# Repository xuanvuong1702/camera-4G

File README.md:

# Camera 4G chạy pin — CAM4G

Camera ngoài trời, pin LFP 10 Ah, 4G, hồng ngoại, phát hiện chuyển động, ngủ sâu và đánh thức từ xa.

> **Bắt đầu đọc từ [`HANDOVER.md`](HANDOVER.md)** — tổng hợp trạng thái, đã/chưa kiểm chứng và việc còn lại.

## Trạng thái

| Hạng mục | Trạng thái |
|---|---|
| Yêu cầu & kiến trúc | Đã chốt |
| Schematic | **ERC 0 lỗi, 0 cảnh báo** |
| PCB | 100×70 mm, 4 lớp, 3 plane (GND/VBAT/+5V), **DRC 0 unconnected / 0 short / 0 clearance** — chỉ còn silk |
| Gerber + drill | Đã xuất, đóng gói `gerber/CAM4G-fab.zip` |
| BOM | 81 dòng, value đúng; kèm BOM mua hàng có MPN |
| CPL | 79 dòng (TP1/TP2 không paste — đúng) |
| Firmware Linux | **17/17 test pass** (mô phỏng) |
| Firmware MCU | **6/6 test host**, build ARM 1720 B |
| Cloud/app | Chưa bắt đầu |

## Quyết định quan trọng

- **720p**, IR ≤ 3 m, ghi local 7 h, không khí 40–45 °C.
- **Core1106G3 N256** (module 30×30, 112 pad) — không dùng dev board Pico Max.
- **Pin LFP 10 Ah** + BMS ngay từ đầu.
- **Vỏ nhôm đúc** — bắt buộc, Core1106 chỉ rated −20…+60 °C.
- **Modem Quectel EC200U-EU** qua UART, breakout cắm header J11; R32/R33 DNP.
- **Hai chế độ ngủ**: "canh gác nhanh" (~40–75 ngày, nhận lệnh 5–15 s) và "tiết kiệm tối đa" (nhiều tháng, chỉ PIR/lịch).
- Sạc bị cấm khi nhiệt độ pin > 40 °C.
- Board **100×70 mm** (80×55 không đủ chỗ cho 81 linh kiện).
- **v5**: sửa U3 sang SON DLC, shunt 0,01 Ω, J2 JST VH 10 A, Q3 AO3400A, VBUS_DET đúng, Q1–Q3 đã nối.

## Cấu trúc

```
4g-camera/
├── HANDOVER.md                   # tổng hợp trạng thái + việc còn lại
├── README.md
├── docs/
│   ├── 00–04                     # phân tích lịch sử (đã lưu)
│   ├── 05-simplification.md      # phương án giảm linh kiện
│   ├── 06-manufacturing.md       # hồ sơ gửi xưởng
│   ├── 07-test-plan.md           # kế hoạch kiểm tra 8 giai đoạn
│   ├── 08-bringup.md             # hướng dẫn cấp nguồn lần đầu
│   ├── 09-modem-ec200u.md        # chọn & đấu modem
│   ├── 10-readiness-audit.md     # rà soát sẵn sàng sản xuất
│   └── 11-cost-estimate.md       # dự tính chi phí lô 5 bộ
├── hardware/
│   ├── POWER.md                  # thiết kế khối nguồn
│   ├── wiring-v2-ipc.md          # kiến trúc & đấu dây
│   ├── bom-prototype-v3.csv      # BOM hệ thống
│   ├── datasheets/               # datasheet gốc
│   └── kicad/CAM4G/              # project, gerber, BOM, CPL, libs, tools
└── firmware/
    ├── linux/                    # app Python + 17 test
    └── mcu/                      # C + host test + target build (CMSIS)
```

## Hồ sơ gửi xưởng

| File | Vị trí |
|---|---|
| Gerber + drill | `hardware/kicad/CAM4G/gerber/CAM4G-fab.zip` |
| BOM | `hardware/kicad/CAM4G/CAM4G-bom.csv` |
| BOM mua hàng (MPN) | `hardware/kicad/CAM4G/CAM4G-bom-procurement.csv` |
| CPL | `hardware/kicad/CAM4G/CAM4G-cpl.csv` |
| Thông số & lắp ráp | `docs/06-manufacturing.md` |

## Nguyên tắc làm việc

- Mọi con số công suất/nhiệt là **ước tính** cho đến khi đo trên board thật.
- Không đoán số chân IC — sai một chân là hỏng board và mất 3 tuần.
- Không tuyên bố "chạy được" khi chưa có phép đo.

## Đã kiểm chứng / chưa

**Đã:** ERC, DRC, BOM↔board, Gerber, firmware test trên host, build ARM.

**Chưa:** chạy trên board thật, I2C slave, dòng ngủ, 7 h ghi ở 60 °C, 4G trên 3 nhà mạng, sạc LFP.

## Việc tiếp theo

1. Chọn mã LCSC cho thụ động (hoặc để JLCPCB map theo value + footprint).
2. Chốt breakout EC200U, camera 20-pin, pin 10 Ah, vỏ.
3. Đặt 5 bộ → làm theo `docs/08-bringup.md`.

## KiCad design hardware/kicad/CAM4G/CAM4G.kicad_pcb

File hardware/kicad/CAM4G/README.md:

# CAM4G — KiCad project (v4 final)

Carrier board cho Core1106 + modem EC200U-EU. **Thiết kế đã route xong và DRC sạch.**

## Trạng thái

| Hạng mục | Kết quả |
|---|---|
| Schematic | Hoàn chỉnh — U1 + nguồn + connector + MCU |
| ERC | **0 lỗi, 0 cảnh báo** |
| PCB | 100 × 70 mm, 4 lớp, **81 footprint** |
| Route | 1278 track + 183 via + plane In1 GND / In2 VBAT / B.Cu +5V |
| DRC | **0 unconnected, 0 short, 0 clearance, 0 track width, 0 copper edge** |
| Lỗi còn lại | 4 silk_edge_clearance + 2 silk_over_copper (chỉ in lụa) |
| Gerber | 28 file + drill, đóng gói `gerber/CAM4G-fab.zip` |
| BOM | 81 dòng, value đúng (lấy từ netlist) |
| CPL | 79 dòng (TP1/TP2 không paste — đúng) |

## File chính

| File | Nội dung |
|---|---|
| `CAM4G.kicad_pro` | Project KiCad 10 |
| `CAM4G.kicad_sch` | Schematic đầy đủ (khổ User 1400×1150) |
| `CAM4G.kicad_pcb` | PCB 100×70, 4 lớp, đã route |
| `CAM4G.kicad_dru` | Rule tuỳ chỉnh |
| `CAM4G.net` | Netlist (85 net chức năng) |
| `CAM4G-bom.csv` | BOM 81 dòng |
| `CAM4G-bom-procurement.csv` | BOM mua hàng, có MPN gợi ý |
| `CAM4G-cpl.csv` | Toạ độ dán |
| `gerber/` | Gerber + drill + `CAM4G-fab.zip` |
| `CAM4G-schematic-preview.pdf` | Xem trước schematic |
| `CAM4G-pcb-preview.pdf` | Xem trước PCB |
| `erc-final.rpt` / `drc-final.rpt` | Báo cáo cuối |
| `libs/` | Symbol Core1106, symbol nguồn, footprint, 3D |
| `tools/` | Script dựng board và nhập route |
| `NETLIST.md` | Bảng kết nối, pinout camera 20P |

## Thông số board

| Thông số | Giá trị |
|---|---|
| Kích thước | 100 × 70 mm |
| Số lớp | 4 |
| Độ dày | 1,6 mm |
| Đồng | 1 oz |
| Bề mặt | ENIG |
| Min trace | 0,15 mm (stub 0,1 mm) |
| Min clearance | 0,14 mm |
| Via | 0,45 mm / khoan 0,3 mm |
| Lỗ khoan | (3,5; 23,2), (95,5), (5,65), (95,65) |

## Các sửa đổi quan trọng

1. **Zone VBAT F.Cu toàn board bị export thành "plane"** → Freerouting bỏ qua net COMP_BOOST.
   Đã bỏ zone trước khi route, route lại, thêm zone B.Cu sau. **Đây là nguyên nhân 2 điểm COMP
   chưa nối tồn tại qua nhiều vòng.**
2. Footprint TPS61088 sửa theo land pattern TI RHL0020A: pad 0,24×0,6 tại ±1,525, EP 2,05.
3. Pad góc U2 giảm 0,24 → 0,23 mm để đủ clearance 0,15 mm (lệch 0,01 mm so với TI).
4. Lỗ khoan dời khỏi L1 và R21.
5. Netclass clearance hạ 0,2 → 0,14 mm; min track 0,1 mm cho stub MIPI.
6. U3 chuyển sang SON DLC 1,5×2 (datasheet); J2 JST VH 10 A; R7 0,01 Ω 2512; Q3 AO3400A; Q1–Q3 nối đúng chân; R34 → VBUS_5V.

## Quy trình dựng lại

```powershell
$py = "C:\Users\vuong\AppData\Local\Programs\KiCad\10.0\bin\python.exe"
$dir = "...\hardware\kicad\CAM4G"
& $py "$dir\tools\build_pcb.py"          # dựng board chưa route
& $py -c "import pcbnew; b=pcbnew.LoadBoard(r'...\CAM4G.kicad_pcb'); pcbnew.ExportSpecctraDSN(b, r'...\CAM4G.dsn')"
# route bằng Freerouting (jar Java 25)
& $py "$dir\tools\ses_import.py"          # nhập .ses
& $py "$dir\tools\post_route_fix.py"      # via + zone VBAT B.Cu
kicad-cli pcb drc ...
```

## Ghi chú

- **MIPI chưa kiểm soát impedance 100 Ω** — rủi ro nếu ảnh lỗi.
- Pad U2 0,23 mm thay vì 0,24 mm — trong dung sai hàn.
- Không còn file backup; lịch sử nằm trong git (`dev`).

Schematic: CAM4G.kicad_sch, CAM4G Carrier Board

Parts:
BT1: CR1220; Battery_Panasonic_CR1220-VCN_Vertical_CircularHoles
C1, C11, C13, C14: 10uF; C_0603_1608Metric
C2, C6, C12, C15, C16, C17, C19: 100nF; C_0603_1608Metric
C3: 3.3uF; C_0603_1608Metric
C4: 47uF; C_0603_1608Metric
C5: 2.2nF; C_0603_1608Metric
C7: 47nF; C_0603_1608Metric
C8: DNP; C_0603_1608Metric; not fitted
C9, C18: 1uF; C_0603_1608Metric
C10: 4.7uF; C_0603_1608Metric
D1: RED; LED_0603_1608Metric
D2: GRN; LED_0603_1608Metric
D3: PWR; LED_0603_1608Metric
D5, D6: BAT54; D_SOD-323
J1: USB-C; USB_C_Receptacle_HRO_TYPE-C-31-M-12
J2: BAT; JST_VH_B2P-VH_1x02_P3.96mm_Vertical
J3: CAM 20P; Hirose_FH12-20S-0.5SH_1x20-1MP_P0.50mm_Horizontal
J4: microSD; microSD_HC_Hirose_DM3AT-SF-PEJM5
J6: PIR; JST_XH_B3B-XH-A_1x03_P2.50mm_Vertical
J7: IR LED; JST_XH_B2B-XH-A_1x02_P2.50mm_Vertical
J8: IR-CUT; JST_XH_B2B-XH-A_1x02_P2.50mm_Vertical
J9, J10: DS18B20; JST_XH_B3B-XH-A_1x03_P2.50mm_Vertical
J11: MODEM; PinHeader_2x06_P1.27mm_Vertical
J12: DEBUG UART; PinHeader_1x03_P2.54mm_Vertical
J13: SWD; PinHeader_1x04_P2.54mm_Vertical
L1: 1.2uH; L_Bourns-SRN8040_8x8.15mm
L2: 2.2uH; L_Bourns-SRN4018
NTC1: 10k B3950; R_0603_1608Metric
Q1: AO3401; SOT-23
Q2: 2N3904; SOT-23
Q3: AO3400A; SOT-23
R1: 178k; R_0603_1608Metric
R2: 56k; R_0603_1608Metric
R3, R6: 267k; R_0603_1608Metric
R4: 64.9k; R_0603_1608Metric
R5: 10.5k; R_0603_1608Metric
R7: 0.01R; R_2512_6332Metric
R8, R9: 4.7k; R_0603_1608Metric
R10: 2.4k; R_0603_1608Metric
R11, R12, R21: 1k; R_0603_1608Metric
R13: 7.15k; R_0603_1608Metric
R14, R15: 5.1k; R_0603_1608Metric
R16, R18, R20: 100k; R_0603_1608Metric
R17, R23, R25, R34, R35: 10k; R_0603_1608Metric
R19: 100R; R_0603_1608Metric
R24, R31, R32, R33: 0R; R_0603_1608Metric
SW1: RESET; SW_SPST_B3S-1000
TP1: TP_3V3; TestPoint_Pad_1.5x1.5mm
TP2: TP_1V8; TestPoint_Pad_1.5x1.5mm
U1: Core1106; Core1106-SMT
U2: TPS61088; VQFN20_3.5
U3: TPS62840; DLC0008B
U4: INA226; MSOP-10_3x3mm_P0.5mm
U5: CN3058E; SOIC-8-1EP_3.9x4.9mm_P1.27mm_EP2.41x3.3mm
U6: STM32L011F4; TSSOP-20_4.4x6.5mm_P0.65mm

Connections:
/+3V3: C11.1, C12.1, C17.1, C18.1, D5.2 (A), J3.19, J3.20, J4.4 (VDD), J6.1, J9.1, J10.1, J11.11, J13.1, L2.2, R8.2, R9.2, R21.1, R23.1, U3.8 (VOS), U4.6 (VS), U6.5 (VDDA), U6.16 (VDD)
/+3V3_RTC: C16.1, D5.1 (K), D6.1 (K), U1.76 (VCC3V3_RTC)
/+5V_MODEM: J11.1, Q1.3 (D)
/+5V_SYS: C4.1, C9.1, J7.1, Q1.2 (S), R1.1, R16.1, U1.79 (VCC5V0_SYS), U1.80 (VCC5V0_SYS), U1.81 (VCC5V0_SYS), U2.14 (VOUT), U2.15 (VOUT), U2.16 (VOUT)
/BOOST_EN: U2.2 (EN), U6.11 (PA5)
/BOOT_BOOST: C6.1, U2.8 (BOOT)
/BT1_P: BT1.1 (+), D6.2 (A)
/BUCK_EN: R31.1, U3.4 (EN)
/CAM_MCLK: J3.2, U1.19 (VI_CIF_CLKO_M0/MIPI_CLK0_OUT/GPIO3_C4_d)
/CAM_MIPI_CK_N: J3.8, U1.9 (VI_CIF_D8_M0/MIPI_CSI_RX_CK0N/LVDS_RX_C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)
/CAM_MIPI_CK_P: J3.7, U1.10 (VI_CIF_D9_M0/MIPI_CSI_RX_CK0P/LVDS_RX_C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)
/CAM_MIPI_D0_N: J3.5, U1.11 (VI_CIF_CLKI_M0/MIPI_CSI_RX_D0N/LVDS_RX_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)
/CAM_MIPI_D0_P: J3.4, U1.12 (VI_CIF_HREF_M0/MIPI_CSI_RX_D0P/LVDS_RX_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)
/CAM_MIPI_D1_N: J3.11, U1.7 (VI_CIF_D6_M0/MIPI_CSI_RX_D1N/LVDS_RX_D1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)
/CAM_MIPI_D1_P: J3.10, U1.8 (VI_CIF_D7_M0/MIPI_CSI_RX_D1P/LVDS_RX_D1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)
/CAM_RESET: J3.16, U1.16 (VI_CIF_D11/UART5_TX_M2/I2C4_SCL_M2/GPIO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)
/CAM_SCL: J3.13, U1.15 (VI_CIF_D13/UART5_RTS_M2/I2C3_SCL_M2/GPI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)
/CAM_SDA: J3.14, U1.14 (VI_CIF_D14/UART5_CTS_M2/I2C3_SDA_M2/GPI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)
/CHG_DONE: D2.1 (K), U5.6 (DONE)
/CHG_STAT: D1.1 (K), U5.7 (CHRG)
/COMP_BOOST: C8.1, R5.1, U2.18 (COMP)
/COMP_MID: C5.1, R5.2
/DBG_RX: J12.2, U1.59 (UART0_TX_M0/PWM2_M0/GPIO0_A1_d)
/DBG_TX: J12.1, U1.58 (UART0_RX_M0/CLK_32K/CLK_REFOUT/RTC_CLKO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)
/FB_BOOST: R1.2, R2.1, U2.17 (FB)
/FSW_BOOST: R3.1, U2.3 (FSW)
/GND: BT1.2 (-), C1.2, C2.2, C3.2, C4.2, C5.2, C7.2, C8.2, C9.2, C10.2, C11.2, C12.2, C13.2, C14.2, C15.2, C16.2, C17.2, C18.2, C19.2, D3.1 (K), J1.A1 (GND), J1.A12 (GND), J1.B1 (GND), J1.B12 (GND), J1.SH (SHIELD), J2.2, J3.1, J3.3, J3.6, J3.9, J3.12, J3.15, J3.17, J3.18, J4.6 (VSS), J4.SH (SHIELD), J6.3, J9.3, J10.3, J11.2, J11.8, J11.12, J12.3, J13.4, NTC1.2, Q2.2 (E), Q3.2 (S), R2.2, R4.2, R6.2, R10.2, R14.2, R15.2, R18.2, R20.2, R24.2, R25.2, R35.2, SW1.2, U1.21 (GND), U1.25 (GND), U1.28 (GND), U1.29 (GND), U1.36 (GND), U1.47 (GND), U1.55 (GND), U1.56 (GND), U1.57 (GND), U1.75 (GND), U1.82 (GND), U1.83 (GND), U1.84 (GND), U1.89 (GND), U1.112 (GND), U2.11 (NC), U2.12 (NC), U2.13 (MODE), U2.20 (AGND), U2.21 (PGND), U3.1 (GND), U3.3 (MODE), U3.6 (STOP), U4.1 (A1), U4.2 (A0), U4.7 (GND), U5.3 (GND), U5.9 (EP), U6.15 (VSS)
/I2C_SCL: R9.1, U1.63 (I2C1_SCL_M0/UART1_RTS_M0/PWM5_M0/GPIO0_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), U4.5 (SCL), U6.17 (PA9)
/I2C_SDA: R8.1, U1.64 (I2C1_SDA_M0/UART1_CTS_M0/PWM6_M0/GPIO0_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), U4.4 (SDA), U6.18 (PA10)
/ILIM_BOOST: R4.1, U2.19 (ILIM)
/INA_ALERT: U4.3 (ALERT), U6.13 (PA7)
/IRCUT_A: J8.1, U1.70 (UART4_RX_M0/PWM3_IR_M1/GPIO1_B0_d)
/IRCUT_B: J8.2, U1.71 (UART4_TX_M0/PWM7_IR_M1/SPI1_CS1_M0/VI_C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)
/IR_GATE: Q3.1 (G), R19.2, R20.1
/IR_LED_K: J7.2, Q3.3 (D)
/IR_PWM: R19.1, U1.60 (PWM3_IR_M0/GPIO0_A2_d)
/ISET: R10.1, U5.2 (ISET)
/LED_CHG_A: D1.2 (A), R11.2
/LED_DONE_A: D2.2 (A), R12.2
/LED_PWR_A: D3.2 (A), R21.2
/MCU_BOOT0: R25.1, U6.1 (PB9)
/MCU_NRST: C19.1, U6.4 (NRST)
/MODEM_B: Q2.1 (B), R17.2, R18.1
/MODEM_EN: R17.1, U6.10 (PA4)
/MODEM_GATE: Q1.1 (G), Q2.3 (C), R16.2
/MODEM_PWRKEY: J11.5, U6.8 (PA2)
/MODEM_RESET: J11.7, U6.2 (PC14)
/MODEM_STATUS: J11.6, U6.9 (PA3)
/MODEM_UART_RX: J11.10, U1.69 (UART1_RX_M0/I2C0_SDA_M0/GPIO1_A4_d)
/MODEM_UART_TX: J11.9, U1.68 (UART1_TX_M0/I2C0_SCL_M0/GPIO1_A3_d)
/ONEWIRE: J9.2, J10.2, U6.7 (PA1)
/PIR_OUT: J6.2, U6.6 (PA0)
/RESET_N: C15.1, R23.2, SW1.1, U1.74 (NPOR)
/SD_CD: R24.1, U1.48 (SDMMC_DET/GPIO3_A1_u)
/SD_CLK: J4.5 (CLK), U1.54 (SDMMC_CLK/UART5_RTS_M0/I2C0_SCL_M2/JTAG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)
/SD_CMD: J4.3 (CMD), U1.53 (SDMMC_CMD/UART5_CTS_M0/I2C0_SDA_M2/JTAG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)
/SD_D0: J4.7 (DAT0), U1.49 (SDMMC_D0/UART2_RX_M0/PWM8_M0/GPIO3_A3_u)
/SD_D1: J4.8 (DAT1), U1.50 (SDMMC_D1/UART2_TX_M0/PWM9_M0/GPIO3_A2_u)
/SD_D2: J4.1 (DAT2), U1.51 (SDMMC_D2/UART5_RX_M0/JTAG_CPU_TCK_M0/JT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)
/SD_D3: J4.2 (DAT3/CD), U1.52 (SDMMC_D3/UART5_TX_M0/JTAG_CPU_TMS_M0/JT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)
/SOC_READY: U1.67 (PWM0_M0/CPU_AVS/VI_CIF_D0_M1/GPIO1_A2_d), U6.12 (PA6)
/SS_BOOST: C7.1, U2.10 (SS)
/SWCLK: J13.3, U6.20 (PA14)
/SWDIO: J13.2, U6.19 (PA13)
/SW_BOOST: C6.2, L1.2, R3.2, U2.4 (SW), U2.5 (SW), U2.6 (SW), U2.7 (SW)
/SW_BUCK: L2.1, U3.7 (SW)
/TEMP_NTC: NTC1.1, R13.1, U5.1 (TEMP)
/TP_1V8: TP2.1, U1.77 (VCC_1V8)
/TP_3V3: TP1.1, U1.78 (VCC_3V3)
/USB_CC1: J1.A5 (CC1), R14.1
/USB_CC2: J1.B5 (CC2), R15.1
/USB_DBG_DM: J1.A7 (D-), J1.B7 (D-)
/USB_DBG_DP: J1.A6 (D+), J1.B6 (D+)
/USB_DM: R33.1, U1.22 (USB_N)
/USB_DP: R32.1, U1.23 (USB_P)
/USB_MODEM_DM: J11.4, R33.2
/USB_MODEM_DP: J11.3, R32.2
/VBAT: C1.1, C2.1, C10.1, C14.1, L1.1, R7.2, R31.2, U2.9 (VIN), U3.2 (VIN), U4.8 (VBUS), U4.9 (IN-), U5.5 (BAT), U5.8 (FB)
/VBAT_BMS: J2.1, R7.1, U4.10 (IN+)
/VBAT_SENSE: U1.26 (SARADC_IN0/GPIO4_C0_z), U6.14 (PB1)
/VBUS_5V: C13.1, J1.A4 (VBUS), J1.A9 (VBUS), J1.B4 (VBUS), J1.B9 (VBUS), R11.1, R12.1, R13.2, R34.1, U5.4 (VIN)
/VBUS_DET: R34.2, R35.1, U1.24 (USB_VBUSDET)
/VCC_BOOST: C3.1, U2.1 (VCC)
/VSET_BUCK: R6.1, U3.5 (VSET)

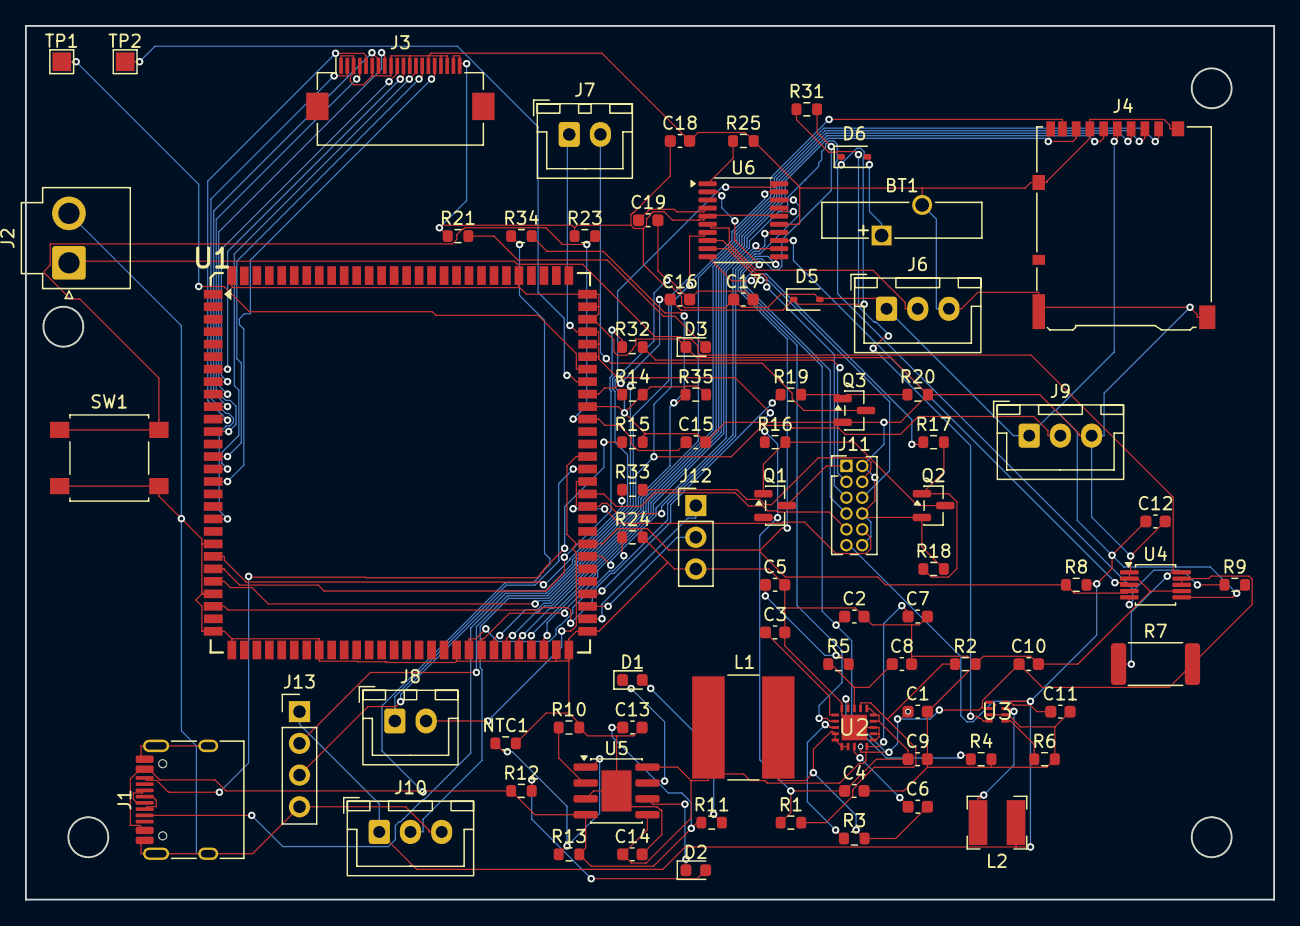
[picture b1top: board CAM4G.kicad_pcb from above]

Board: 4 copper layers, 100.0 x 70.0 mm, 81 parts (0 on the bottom side), 84 nets.

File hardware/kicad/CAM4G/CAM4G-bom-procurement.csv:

Value,Footprint,Qty,References,Suggested MPN,Manufacturer,Notes
CR1220,Battery_Panasonic_CR1220-VCN_Vertical_CircularHoles,1,BT1,CR1220-VCN,Panasonic,holder + cell
10uF,C_0603_1608Metric,4,C1 C11 C13 C14,,,select by spec
100nF,C_0603_1608Metric,7,C2 C6 C12 C15 C16 C17 C19,,,select by spec
3.3uF,C_0603_1608Metric,1,C3,,,select by spec
47uF,C_0603_1608Metric,1,C4,,,select by spec
2.2nF,C_0603_1608Metric,1,C5,,,select by spec
47nF,C_0603_1608Metric,1,C7,,,select by spec
DNP,C_0603_1608Metric,1,C8,,,select by spec
1uF,C_0603_1608Metric,2,C9 C18,,,select by spec
4.7uF,C_0603_1608Metric,1,C10,,,select by spec
RED,LED_0603_1608Metric,1,D1,,,select by spec
GRN,LED_0603_1608Metric,1,D2,,,select by spec
PWR,LED_0603_1608Metric,1,D3,,,select by spec
BAT54,D_SOD-323,2,D5 D6,BAT54,onsemi,Schottky
USB-C,USB_C_Receptacle_HRO_TYPE-C-31-M-12,1,J1,TYPE-C-31-M-12,HRO,16P
BAT,JST_XH_B2B-XH-A_1x02_P2.50mm_Vertical,1,J2,,,select by spec
CAM 20P,Hirose_FH12-20S-0.5SH_1x20-1MP_P0.50mm_Horizontal,1,J3,FH12-20S-0.5SH,Hirose,FPC 20P 0.5mm
microSD,microSD_HC_Hirose_DM3AT-SF-PEJM5,1,J4,DM3AT-SF-PEJM5,Hirose,push-push
PIR,JST_XH_B3B-XH-A_1x03_P2.50mm_Vertical,1,J6,,,select by spec
IR LED,JST_XH_B2B-XH-A_1x02_P2.50mm_Vertical,1,J7,,,select by spec
IR-CUT,JST_XH_B2B-XH-A_1x02_P2.50mm_Vertical,1,J8,,,select by spec
DS18B20,JST_XH_B3B-XH-A_1x03_P2.50mm_Vertical,2,J9 J10,,,select by spec
MODEM,PinHeader_2x06_P1.27mm_Vertical,1,J11,,,select by spec
DEBUG UART,PinHeader_1x03_P2.54mm_Vertical,1,J12,,,select by spec
SWD,PinHeader_1x04_P2.54mm_Vertical,1,J13,,,select by spec
1.2uH,L_Bourns-SRN8040_8x8.15mm,1,L1,SRN8040-1R2M,Bourns,verify Isat >= 9 A
2.2uH,L_Bourns-SRN4018,1,L2,SRN4018-2R2M,Bourns,verify
10k B3950,R_0603_1608Metric,1,NTC1,,,select by spec
AO3401,SOT-23,1,Q1,AO3401A,AOS,P-MOS
2N3904,SOT-23,1,Q2,2N3904,onsemi,NPN
IRLZ44N,SOT-23,1,Q3,IRLZ44NPBF,Infineon,N-MOS logic level
178k,R_0603_1608Metric,1,R1,,,select by spec
56k,R_0603_1608Metric,1,R2,,,select by spec
267k,R_0603_1608Metric,2,R3 R6,,,select by spec
64.9k,R_0603_1608Metric,1,R4,,,select by spec
10.5k,R_0603_1608Metric,1,R5,,,select by spec
0.05R,R_1206_3216Metric,1,R7,0.05R 1% 1W,any,current shunt
4.7k,R_0603_1608Metric,2,R8 R9,,,select by spec
1.2k,R_0603_1608Metric,1,R10,,,select by spec
1k,R_0603_1608Metric,3,R11 R12 R21,,,select by spec
7.15k,R_0603_1608Metric,1,R13,,,select by spec
5.1k,R_0603_1608Metric,2,R14 R15,,,select by spec
100k,R_0603_1608Metric,3,R16 R18 R20,,,select by spec
10k,R_0603_1608Metric,5,R17 R23 R25 R34 R35,,,select by spec
100R,R_0603_1608Metric,1,R19,,,select by spec
0R,R_0603_1608Metric,4,R24 R31 R32 R33,,,select by spec
RESET,SW_SPST_B3S-1000,1,SW1,B3S-1000,Omron,tactile
TP_3V3,TestPoint_Pad_1.5x1.5mm,1,TP1,,,select by spec
TP_1V8,TestPoint_Pad_1.5x1.5mm,1,TP2,,,select by spec
Core1106,Core1106-SMT,1,U1,Core1106G3 N256,Luckfox,module 30x30 112 pad
TPS61088,,1,U2,,,select by spec
TPS62840,Texas_DSG0008A_WSON-8-1EP_2x2mm_P0.5mm_EP0.9x1.6mm,1,U3,TPS62840DLC,TI,WSON-8
INA226,MSOP-10_3x3mm_P0.5mm,1,U4,INA226AIDGSR,TI,VSSOP-10
CN3058E,SOIC-8-1EP_3.9x4.9mm_P1.27mm_EP2.41x3.3mm,1,U5,CN3058E,Consonance,eSOP-8
STM32L011F4,TSSOP-20_4.4x6.5mm_P0.65mm,1,U6,STM32L011F4P6,ST,TSSOP-20

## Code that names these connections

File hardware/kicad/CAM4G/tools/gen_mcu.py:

import re
import uuid

BASE = r"C:\Users\vuong\Documents\deepseek-harness\default-workspace\4g-camera\hardware\kicad\CAM4G"
LIBDIR = r"C:\Users\vuong\AppData\Local\Programs\KiCad\10.0\share\kicad\symbols"
ROOT = BASE + r"\CAM4G.kicad_sch"


def match_block(text, start_idx):
    depth = 0
    j = start_idx
    while True:
        c = text[j]
        if c == '(':
            depth += 1
        elif c == ')':
            depth -= 1
            if depth == 0:
                return j
        j += 1


def extract(text, name):
    key = f'(symbol "{name}"'
    i = text.index(key)
    j = match_block(text, i)
    return text[i:j + 1]


def pins_of(block):
    out = []
    pat = re.compile(r'\(pin\s+\S+\s+\S+\s+\(at\s+([-\d.]+)\s+([-\d.]+)\s+([-\d.]+)\).*?\(number\s+"([^"]+)"', re.S)
    for m in pat.finditer(block):
        out.append((m.group(4), float(m.group(1)), float(m.group(2))))
    return out


# ---- MCU symbol ----
MCU_PINS = [
    ("1", "PB9"), ("2", "PC14"), ("3", "PC15"), ("4", "NRST"), ("5", "VDDA"),
    ("6", "PA0"), ("7", "PA1"), ("8", "PA2"), ("9", "PA3"), ("10", "PA4"),
    ("11", "PA5"), ("12", "PA6"), ("13", "PA7"), ("14", "PB1"), ("15", "VSS"),
    ("16", "VDD"), ("17", "PA9"), ("18", "PA10"), ("19", "PA13"), ("20", "PA14"),
]


def make_mcu_symbol():
    n = len(MCU_PINS)
    half = n // 2
    height = half * 2.54 + 5.08
    top = height / 2 - 2.54
    L = ['\t(symbol "CAM4G:STM32L011F4"', '\t\t(exclude_from_sim no)', '\t\t(in_bom yes)', '\t\t(on_board yes)',
         f'\t\t(property "Reference" "U" (at 0 {height/2+2.54:.2f} 0) (effects (font (size 1.27 1.27))))',
         f'\t\t(property "Value" "STM32L011F4" (at 0 {height/2+5.08:.2f} 0) (effects (font (size 1.27 1.27))))',
         '\t\t(property "Footprint" "Package_SO:TSSOP-20_4.4x6.5mm_P0.65mm" (at 0 0 0) (effects (font (size 1.27 1.27)) (hide yes)))',
         '\t\t(property "Datasheet" "" (at 0 0 0) (effects (font (size 1.27 1.27)) (hide yes)))',
         '\t\t(property "Description" "" (at 0 0 0) (effects (font (size 1.27 1.27)) (hide yes)))',
         '\t\t(symbol "STM32L011F4_0_1"',
         f'\t\t\t(rectangle (start -10.16 {height/2:.2f}) (end 10.16 {-height/2:.2f}) (stroke (width 0.254) (type default)) (fill (type background)))',
         '\t\t)',
         '\t\t(symbol "STM32L011F4_1_1"']
    # pins: first 10 left, next 10 right
    body_pins = []
    for i, (num, nm) in enumerate(MCU_PINS):
        if i < half:
            y = top - i * 2.54
            body_pins.append((num, nm, -15.24, y, 0))
        else:
            y = top - (i - half) * 2.54
            body_pins.append((num, nm, 15.24, y, 180))
    for num, nm, x, y, ang in body_pins:
        L.append(f'\t\t\t(pin passive line (at {x:.2f} {y:.2f} {ang}) (length 5.08)')
        L.append(f'\t\t\t\t(name "{nm}" (effects (font (size 1.27 1.27))))')
        L.append(f'\t\t\t\t(number "{num}" (effects (font (size 1.27 1.27))))')
        L.append('\t\t\t)')
    L.append('\t\t)')
    L.append('\t)')
    return "\n".join(L), [(p[0], p[2], p[3]) for p in body_pins]


mcu_text = open(f"{LIBDIR}\\MCU_ST_STM32L0.kicad_sym", encoding="utf-8").read()
mcu_block = extract(mcu_text, "STM32L011F_3-4_Px").replace(
    '(symbol "STM32L011F_3-4_Px"', '(symbol "MCU_ST_STM32L0:STM32L011F_3-4_Px"', 1)
mcu_pins = pins_of(mcu_block)
MCU_LIB = "MCU_ST_STM32L0:STM32L011F_3-4_Px"

# ---- other symbols ----
dev_text = open(f"{LIBDIR}\\Device.kicad_sym", encoding="utf-8").read()
extra = {}
for nm in ["Battery_Cell", "D_Schottky", "R", "C"]:
    b = extract(dev_text, nm).replace(f'(symbol "{nm}"', f'(symbol "Device:{nm}"', 1)
    extra[f"Device:{nm}"] = b

conn_text = open(f"{LIBDIR}\\Connector_Generic.kicad_sym", encoding="utf-8").read()
for nm in ["Conn_01x03", "Conn_01x04"]:
    b = extract(conn_text, nm).replace(f'(symbol "{nm}"', f'(symbol "Connector_Generic:{nm}"', 1)
    extra[f"Connector_Generic:{nm}"] = b

conntext = open(f"{LIBDIR}\\Connector.kicad_sym", encoding="utf-8").read()
b = extract(conntext, "TestPoint").replace('(symbol "TestPoint"', '(symbol "Connector:TestPoint"', 1)
extra["Connector:TestPoint"] = b

root = open(ROOT, encoding="utf-8").read()
ROOT_UUID = re.search(r'\(uuid "([0-9a-f\-]+)"\)', root).group(1)

pin_maps = {k: pins_of(v) for k, v in extra.items()}
pin_maps[MCU_LIB] = mcu_pins


def sym_instance(ref, val, lib, x, y, nets, dnp=False, ref_dy=-12):
    x = round(x / 1.27) * 1.27
    y = round(y / 1.27) * 1.27
    u = str(uuid.uuid4())
    L = ["\t(symbol", f'\t\t(lib_id "{lib}")', f'\t\t(at {x} {y} 0)', "\t\t(unit 1)",
         "\t\t(exclude_from_sim no)", "\t\t(in_bom yes)", "\t\t(on_board yes)",
         f'\t\t(dnp {"yes" if dnp else "no"})', f'\t\t(uuid "{u}")',
         f'\t\t(property "Reference" "{ref}" (at {x} {y+ref_dy} 0) (effects (font (size 1.27 1.27))))',
         f'\t\t(property "Value" "{val}" (at {x} {y+ref_dy+2.54} 0) (effects (font (size 1.27 1.27))))',
         f'\t\t(property "Footprint" "" (at {x} {y} 0) (effects (font (size 1.27 1.27)) (hide yes)))',
         f'\t\t(property "Datasheet" "" (at {x} {y} 0) (effects (font (size 1.27 1.27)) (hide yes)))']
    for num, _, _ in pin_maps[lib]:
        L.append(f'\t\t(pin "{num}" (uuid "{uuid.uuid4()}"))')
    L += ["\t\t(instances", '\t\t\t(project ""', f'\t\t\t\t(path "/{ROOT_UUID}"',
          f'\t\t\t\t\t(reference "{ref}")', "\t\t\t\t\t(unit 1)", "\t\t\t\t)", "\t\t\t)", "\t\t)", "\t)"]
    body = "\n".join(L)

    labels = []
    for num, px, py in pin_maps[lib]:
        ax = x + px
        ay = y - py
        net = nets.get(num)
        if not net:
            labels.append(f'\t(no_connect (at {ax:.3f} {ay:.3f}) (uuid "{uuid.uuid4()}"))')
            continue
        labels.append(f'\t(label "{net}" (at {ax:.3f} {ay:.3f} 0)\n'
                      f'\t\t(effects (font (size 1.0 1.0)) (justify left bottom))\n'
                      f'\t\t(uuid "{uuid.uuid4()}")\n\t)')
    return body, labels


COMPS = []
COMPS.append(("U6", "STM32L011F4", MCU_LIB, 200, 900, {
    "1": "MCU_BOOT0", "2": "MODEM_RESET", "3": None, "4": "MCU_NRST", "5": "+3V3",
    "6": "PIR_OUT", "7": "ONEWIRE", "8": "MODEM_PWRKEY", "9": "MODEM_STATUS",
    "10": "MODEM_EN", "11": "BOOST_EN", "12": "SOC_READY", "13": "INA_ALERT",
    "14": "VBAT_SENSE", "15": "GND", "16": "+3V3", "17": "I2C_SCL",
    "18": "I2C_SDA", "19": "SWDIO", "20": "SWCLK",
}))
COMPS.append(("R25", "10k", "Device:R", 140, 980, {"1": "MCU_BOOT0", "2": "GND"}))
COMPS.append(("C17", "100nF", "Device:C", 180, 980, {"1": "+3V3", "2": "GND"}))
COMPS.append(("C18", "1uF", "Device:C", 220, 980, {"1": "+3V3", "2": "GND"}))
COMPS.append(("C19", "100nF", "Device:C", 260, 980, {"1": "MCU_NRST", "2": "GND"}))
COMPS.append(("J12", "DEBUG UART", "Connector_Generic:Conn_01x03", 320, 980, {"1": "DBG_TX", "2": "DBG_RX", "3": "GND"}))
COMPS.append(("J13", "SWD", "Connector_Generic:Conn_01x04", 380, 980, {"1": "+3V3", "2": "SWDIO", "3": "SWCLK", "4": "GND"}))
COMPS.append(("D5", "BAT54", "Device:D_Schottky", 440, 980, {"2": "+3V3", "1": "+3V3_RTC"}))
COMPS.append(("D6", "BAT54", "Device:D_Schottky", 480, 980, {"2": "BT1_P", "1": "+3V3_RTC"}))
COMPS.append(("BT1", "CR1220", "Device:Battery_Cell", 520, 980, {"1": "BT1_P", "2": "GND"}))
COMPS.append(("C16", "100nF", "Device:C", 560, 980, {"1": "+3V3_RTC", "2": "GND"}))
COMPS.append(("R31", "0R", "Device:R", 600, 980, {"1": "BUCK_EN", "2": "VBAT"}))
COMPS.append(("R32", "0R", "Device:R", 640, 980, {"1": "USB_DP", "2": "USB_MODEM_DP"}))
COMPS.append(("R33", "0R", "Device:R", 680, 980, {"1": "USB_DM", "2": "USB_MODEM_DM"}))
COMPS.append(("R34", "10k", "Device:R", 720, 980, {"1": "+5V_SYS", "2": "VBUS_DET"}))
COMPS.append(("R35", "10k", "Device:R", 760, 980, {"1": "VBUS_DET", "2": "GND"}))
COMPS.append(("TP1", "TP_3V3", "Connector:TestPoint", 800, 980, {"1": "TP_3V3"}))
COMPS.append(("TP2", "TP_1V8", "Connector:TestPoint", 840, 980, {"1": "TP_1V8"}))

blocks = []
for ref, val, lib, x, y, nets in COMPS:
    if lib not in pin_maps:
        continue
    b, l = sym_instance(ref, val, lib, x, y, nets, ref_dy=(16 if lib == MCU_LIB else -12))
    blocks.append(b)
    blocks.extend(l)

new_libs = [mcu_block] + [b for n, b in extra.items() if f'(symbol "{n}"' not in root]
i = root.index("(lib_symbols")
j = match_block(root, i)
root = root[:j] + "\n" + "\n".join(new_libs) + "\n\t" + root[j:]

k = root.index("\t(sheet_instances")
root = root[:k] + "\n".join(blocks) + "\n" + root[k:]

root = root.replace('(paper "A0")', '(paper "User" 1400 1150)')

open(ROOT, "w", encoding="utf-8").write(root)
print("mcu added; comps", len(COMPS), "libs", len(new_libs))
